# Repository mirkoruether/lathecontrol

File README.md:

# Pimp your lathe!
bla bla will be added later.

## Software Libraries
#### RotaryEncoder
https://github.com/mathertel/RotaryEncoder
http://www.mathertel.de/Arduino/RotaryEncoderLibrary.aspx

#### Display
http://www.lcdwiki.com/3.5inch_Arduino_Display-UNO#Program_Download
https://github.com/lcdwiki/LCDWIKI_gui
https://github.com/lcdwiki/LCDWIKI_kbv
https://github.com/adafruit/Adafruit_TouchScreen

## Hardware
#### Measuring Sticks (German):
https://www.wabeco-remscheid.de/catalog/category/view/s/anbaumessschieber/id/562/

#### Arduino Mega2560:
https://store.arduino.cc/arduino-mega-2560-rev3

#### Display
http://www.lcdwiki.com/3.5inch_Arduino_Display-UNO
https://www.amazon.de/gp/product/B07K2YCSJD/

## Other Links
http://www.mtahlers.de/index.php/diverses/messschieberanzeige

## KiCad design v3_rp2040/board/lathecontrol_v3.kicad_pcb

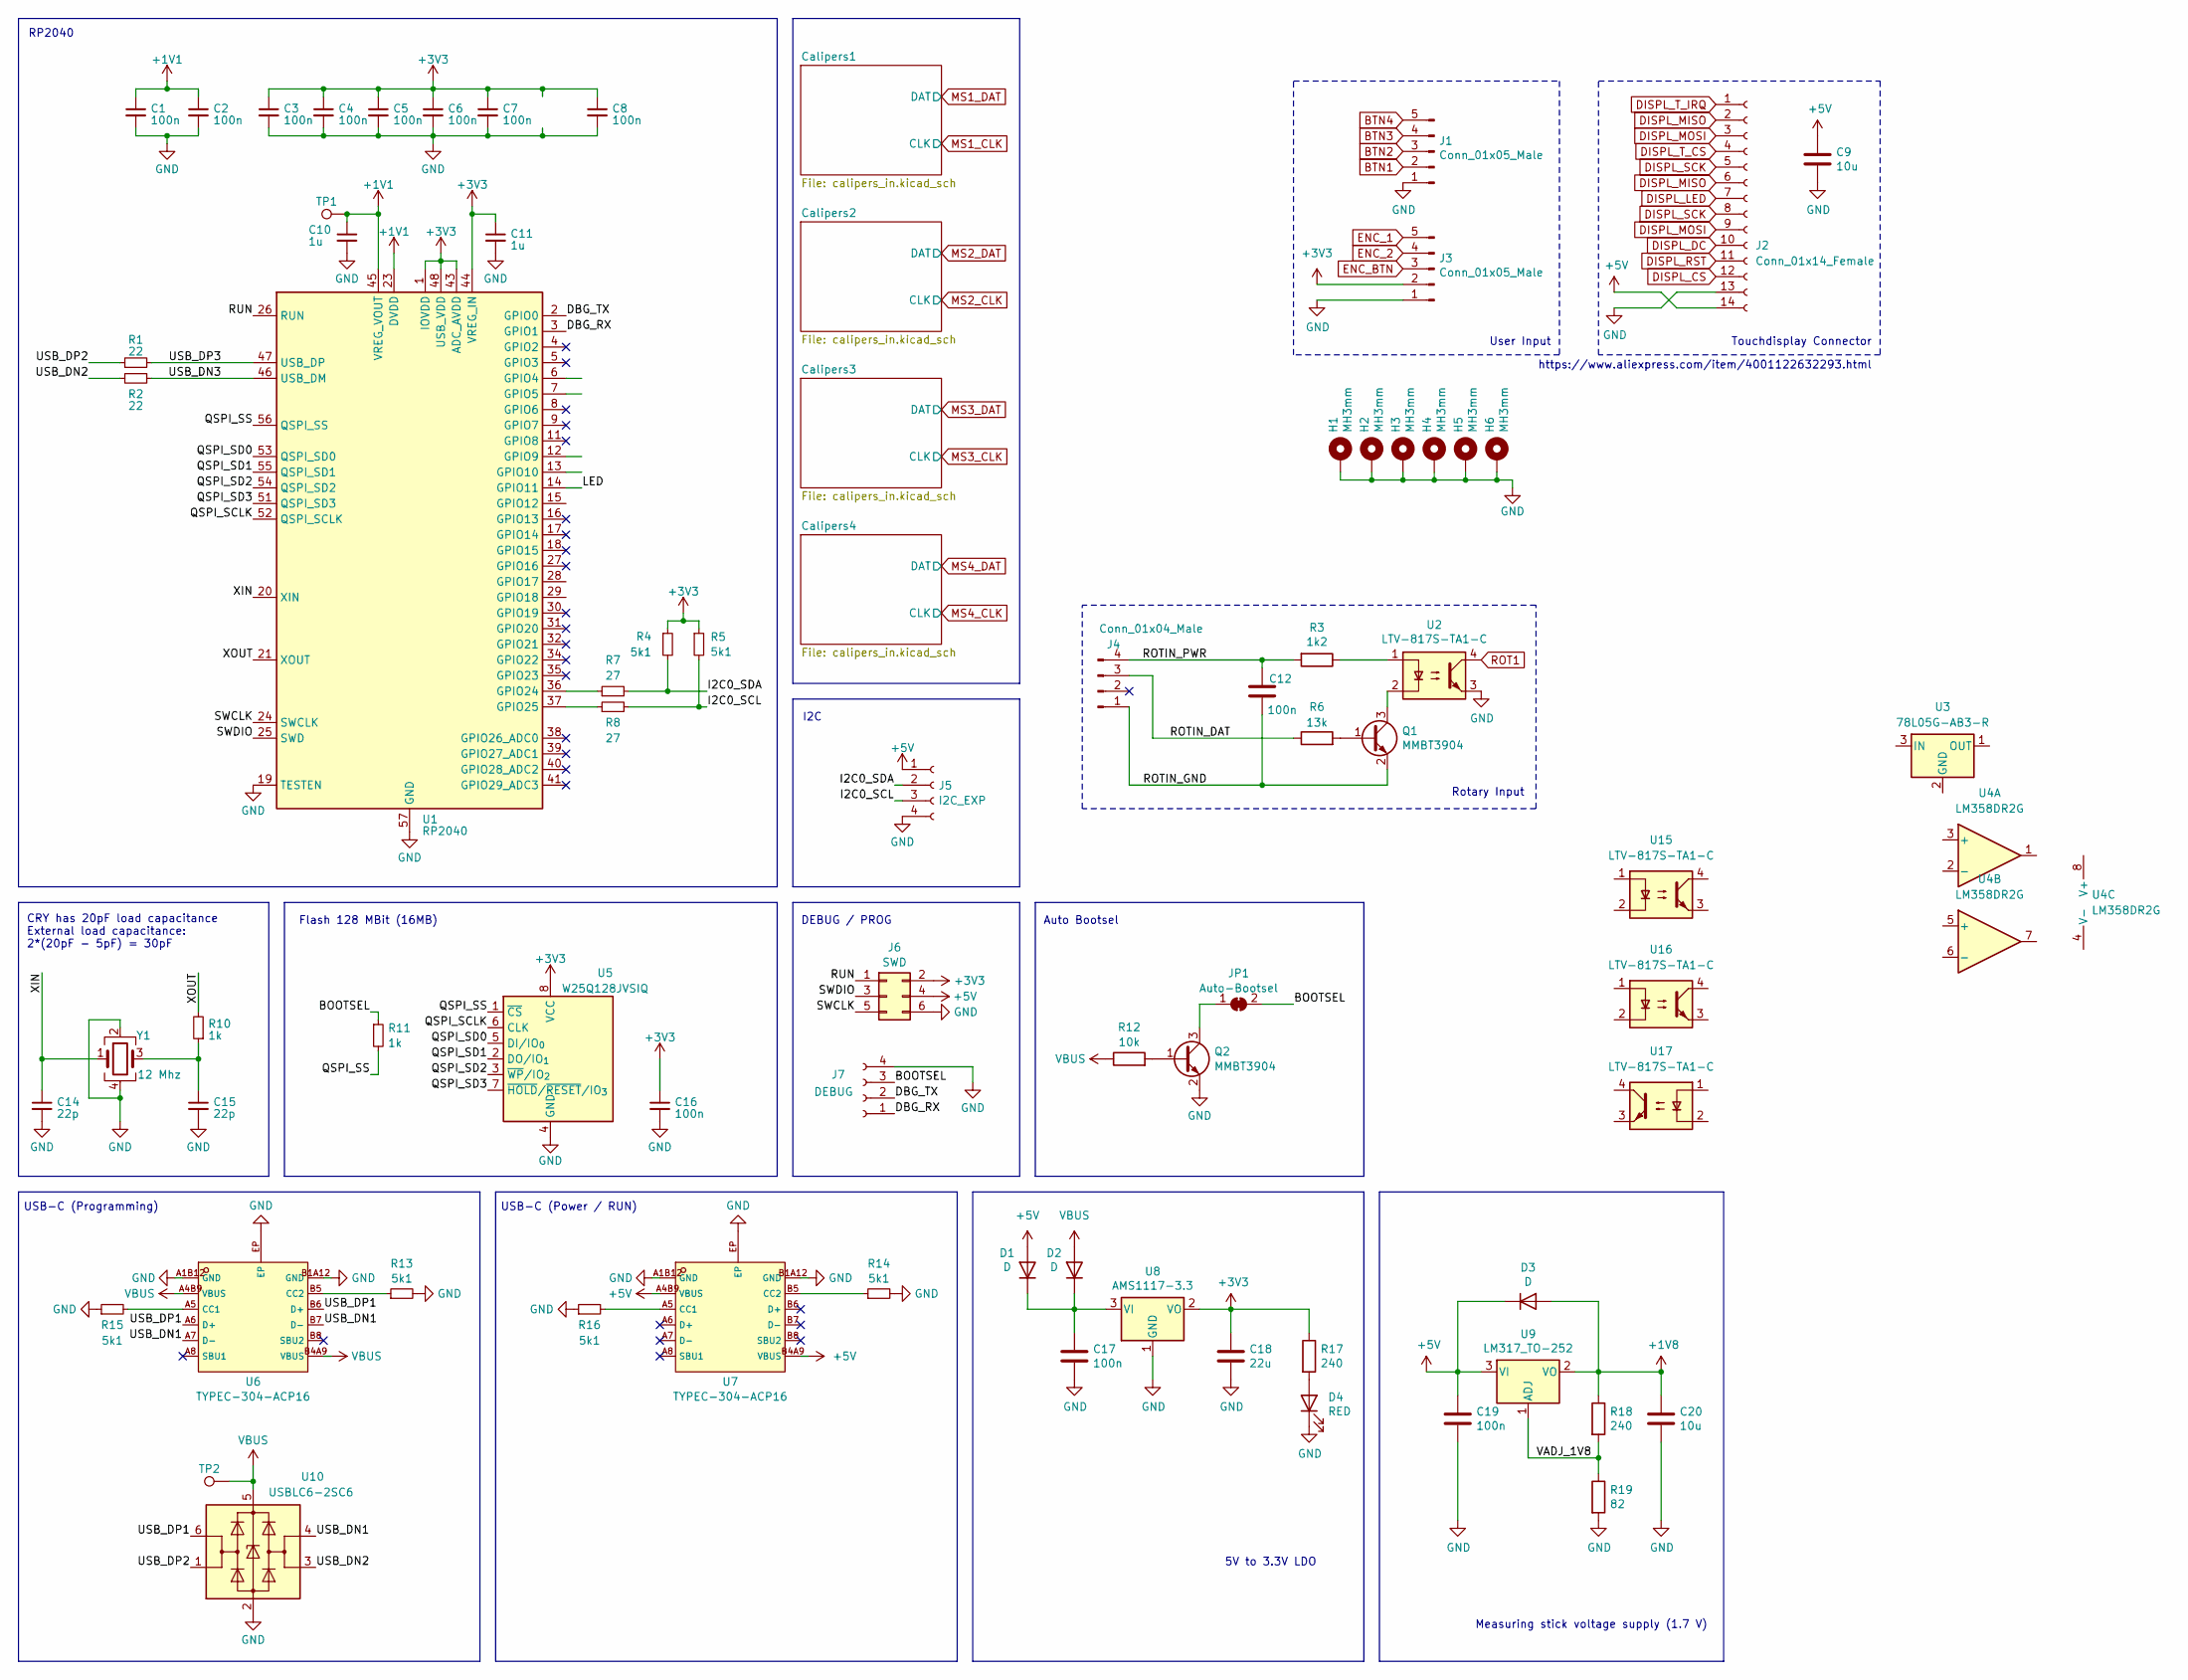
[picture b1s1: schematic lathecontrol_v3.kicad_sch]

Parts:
C1, C2, C3, C4, C5, C6, C7, C8, C16: 100n; C_0402_1005Metric; LCSC C1525
C9, C20: 10u; C_0805_2012Metric; LCSC C13585
C10, C11: 1u; C_0402_1005Metric; LCSC C52923
C12, C17, C19: 100n; C_0603_1608Metric; LCSC C14663
C14, C15: 22p; C_0402_1005Metric; LCSC C1555
C18: 22u; C_0805_2012Metric; LCSC C45783
D1, D2, D3: D; D_SOD-123F; LCSC C64898
D4: RED; LED_0603_1608Metric; LCSC C2286
H1, H2, H3, H4, H5, H6: MH3mm; MountingHole_3mm_Pad
J1: Conn_01x05_Male; PinHeader_1x06_P2.54mm_Horizontal
J2: Conn_01x14_Female; PinSocket_1x14_P2.54mm_Vertical
J3: Conn_01x05_Male; PinHeader_1x05_P2.54mm_Horizontal
J4: Conn_01x04_Male; PinHeader_1x04_P2.54mm_Horizontal
J5: I2C_EXP; PinHeader_1x04_P2.54mm_Vertical; LCSC C2691448
J6: SWD; PinHeader_2x03_P2.54mm_Vertical; LCSC C65114
J7: DEBUG; PinHeader_1x04_P2.54mm_Vertical; LCSC C2691448
JP1: Auto-Bootsel; R_0603_1608Metric; LCSC C21189
Q1: MMBT3904; SOT-23
Q2: MMBT3904; SOT-23; LCSC C20526
R1, R2: 22; R_0402_1005Metric; LCSC C25092
R3: 1k2; R_0805_2012Metric; LCSC C17379
R4, R5, R13, R14, R15, R16: 5k1; R_0603_1608Metric; LCSC C23186
R6: 13k; R_0603_1608Metric; LCSC C22797
R7, R8: 27; R_0603_1608Metric; LCSC C25190
R10, R11: 1k; R_0402_1005Metric; LCSC C11702
R12: 10k; R_0402_1005Metric; LCSC C25744
R17, R18: 240; R_0603_1608Metric; LCSC C23350
R19: 82; R_0603_1608Metric; LCSC C23255
TP1, TP2: TestPoint; TestPoint_Pad_D1.5mm
U1: RP2040; RP2040-QFN-56; LCSC C2040
U2, U15, U16, U17: LTV-817S-TA1-C; SMDIP-4_W9.53mm; LCSC C109227
U3: 78L05G-AB3-R; SOT-89-3; LCSC C71136
U4: LM358DR2G; SOIC-8_3.9x4.9mm_P1.27mm; LCSC C7950
U5: W25Q128JVSIQ; SOIC-8_5.3x5.3mm_P1.27mm; LCSC C97521
U6, U7: TYPEC-304-ACP16; USB-C-SMD_TYPE-C-16P-1; LCSC C2982555
U8: AMS1117-3.3; SOT-223-3_TabPin2; LCSC C6186
U9: LM317_TO-252; TO-252-2; LCSC C75510
U10: USBLC6-2SC6; SOT-23-6; LCSC C2827654
Y1: 12 Mhz; OSC-SMD_4P-L3.2-W2.5-BL; LCSC C9002

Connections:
+1V1: C1.1, C2.1, C10.1, TP1.1 (1_1), U1.23 (DVDD), U1.45 (VREG_VOUT), U1.50 (DVDD)
+1V8: C20.1, D3.2 (A), R18.1, U9.2 (VO); also elsewhere on the board
+3V3: C3.1, C4.1, C5.1, C6.1, C7.1, C8.1, C11.1, C16.1, C18.1, J3.2, J6.2, R4.1, R5.1, R17.1, U1.1 (IOVDD), U1.10 (IOVDD), U1.22 (IOVDD), U1.33 (IOVDD), U1.42 (IOVDD), U1.43 (ADC_AVDD), U1.44 (VREG_IN), U1.48 (USB_VDD), U1.49 (IOVDD), U5.8 (VCC), U8.2 (VO); also elsewhere on the board
+5V: C9.1, C19.1, D1.2 (A), D3.1 (K), J2.14, J5.1, J6.4, U7.A4B9 (VBUS), U7.B4A9 (VBUS), U9.3 (VI)
/BOOTSEL: J7.3, JP1.2 (B), R11.1
/DBG_RX: J7.1, U1.3 (GPIO1)
/DBG_TX: J7.2, U1.2 (GPIO0)
/I2C0_SCL: J5.3, R5.2, R8.2
/I2C0_SDA: J5.2, R4.2, R7.2
/LED: U1.14 (GPIO11)
/QSPI_SCLK: U1.52 (QSPI_SCLK), U5.6 (CLK)
/QSPI_SD0: U1.53 (QSPI_SD0), U5.5 (DI/IO_{0})
/QSPI_SD1: U1.55 (QSPI_SD1), U5.2 (DO/IO_{1})
/QSPI_SD2: U1.54 (QSPI_SD2), U5.3 (~WP/IO_{2})
/QSPI_SD3: U1.51 (QSPI_SD3), U5.7 (~HOLD/~RESET/IO_{3})
/QSPI_SS: R11.2, U1.56 (QSPI_SS), U5.1 (~CS)
/ROTIN_DAT: J4.3, R6.1
/ROTIN_GND: C12.2, J4.1, Q1.2 (E)
/ROTIN_PWR: C12.1, J4.4, R3.2
/RUN: J6.1, U1.26 (RUN)
/SWCLK: J6.5, U1.24 (SWCLK)
/SWDIO: J6.3, U1.25 (SWD)
/USB_DN1: U6.A7 (D-), U6.B7 (D-), U10.4 (I/O2)
/USB_DN2: R2.2, U10.3 (I/O2)
/USB_DN3: R2.1, U1.46 (USB_DM)
/USB_DP1: U6.A6 (D+), U6.B6 (D+), U10.6 (I/O1)
/USB_DP2: R1.1, U10.1 (I/O1)
/USB_DP3: R1.2, U1.47 (USB_DP)
/VADJ_1V8: R18.2, R19.1, U9.1 (ADJ)
/XIN: C14.1, U1.20 (XIN), Y1.1
/XOUT: R10.2, U1.21 (XOUT)
BTN1: J1.2
BTN2: J1.3
BTN3: J1.4
BTN4: J1.5
DISPL_CS: J2.12
DISPL_DC: J2.10
DISPL_LED: J2.7
DISPL_MISO: J2.2, J2.6
DISPL_MOSI: J2.3, J2.9
DISPL_RST: J2.11
DISPL_SCK: J2.5, J2.8
DISPL_T_CS: J2.4
DISPL_T_IRQ: J2.1
ENC_1: J3.5
ENC_2: J3.4
ENC_BTN: J3.3
GND: C1.2, C2.2, C3.2, C4.2, C5.2, C6.2, C7.2, C8.2, C9.2, C10.2, C11.2, C14.2, C15.2, C16.2, C17.2, C18.2, C19.2, C20.2, D4.1 (K), H1.1 (1_1), H2.1 (1_1), H3.1 (1_1), H4.1 (1_1), H5.1 (1_1), H6.1 (1_1), J1.1, J2.13, J3.1, J5.4, J6.6, J7.4, Q2.2 (E), R13.2, R14.2, R15.1, R16.1, R19.2, U1.19 (TESTEN), U1.57 (GND), U2.3, U5.4 (GND), U6.A1B12 (GND), U6.B1A12 (GND), U6.EP, U7.A1B12 (GND), U7.B1A12 (GND), U7.EP, U8.1 (GND), U10.2 (GND), Y1.2, Y1.4; also elsewhere on the board
unnamed: C15.1, R10.1, Y1.3
unnamed: C17.1, D1.1 (K), D2.1 (K), U8.3 (VI)
unnamed: D4.2 (A), R17.2
unnamed: JP1.1 (A), Q2.3 (C)
unnamed: Q1.1 (B), R6.2
unnamed: Q1.3 (C), U2.2
unnamed: Q2.1 (B), R12.2
unnamed: R3.1, U2.1
unnamed: R7.1, U1.36 (GPIO24)
unnamed: R8.1, U1.37 (GPIO25)
unnamed: R15.2, U6.A5 (CC1)
unnamed: R13.1, U6.B5 (CC2)
unnamed: R16.2, U7.A5 (CC1)
unnamed: R14.1, U7.B5 (CC2)
ROT1: U2.4
VBUS: D2.2 (A), R12.1, TP2.1 (1_1), U6.A4B9 (VBUS), U6.B4A9 (VBUS), U10.5 (VBUS)

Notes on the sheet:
5V to 3.3V LDO
RP2040
Rotary Input
Flash 128 MBit (16MB)
https://www.aliexpress.com/item/4001122632293.html
USB-C (Programming)
Touchdisplay Connector
I2C
CRY has 20pF load capacitance External load capacitance: 2*(20pF - 5pF) = 30pF
Measuring stick voltage supply (1.7 V)
Auto Bootsel
USB-C (Power / RUN)
User Input
DEBUG / PROG

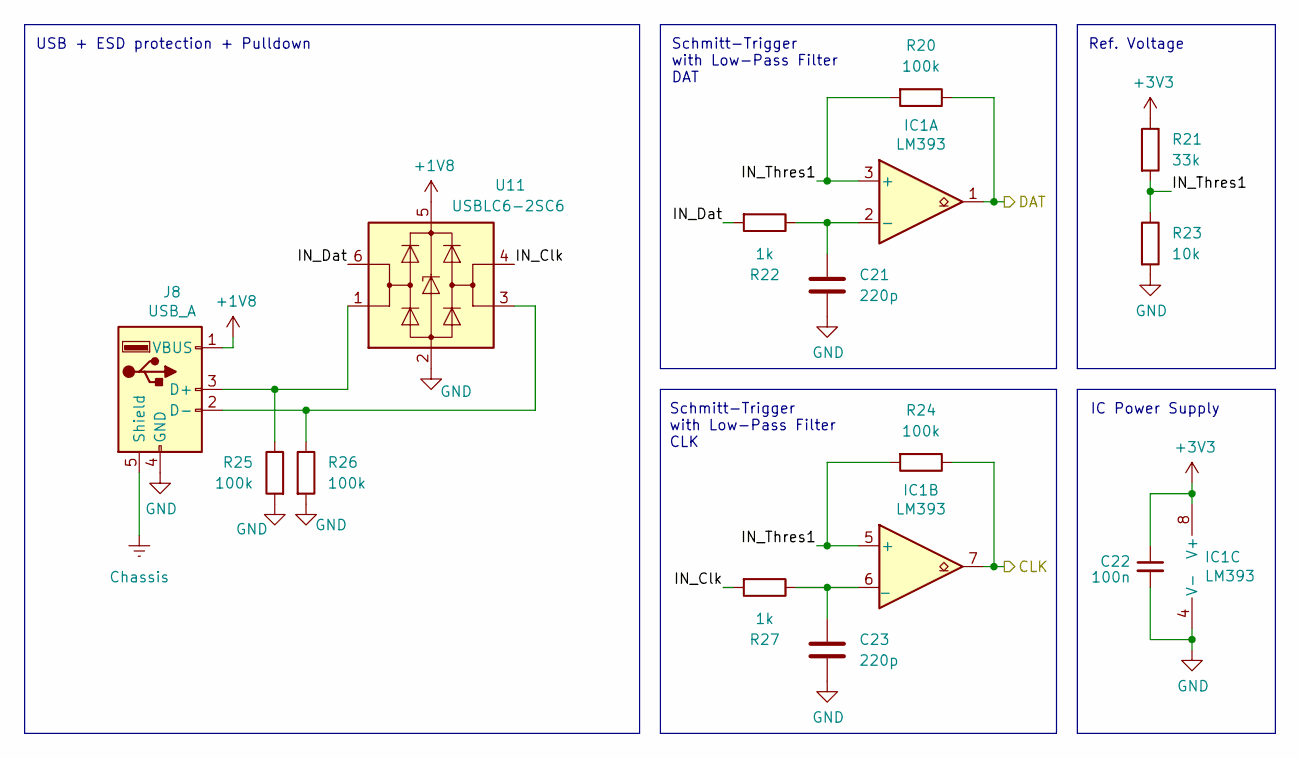
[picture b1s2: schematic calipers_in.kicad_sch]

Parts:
C21, C23: 220p; C_0402_1005Metric; LCSC C1530
C22: 100n; C_0402_1005Metric; LCSC C1525
IC1: LM393; SOIC-8_3.9x4.9mm_P1.27mm
J8: USB_A; USB_A_Upright_C26235; LCSC C26235
R20, R24, R25, R26: 100k; R_0402_1005Metric; LCSC C25741
R21: 33k; R_0402_1005Metric; LCSC C25779
R22, R27: 1k; R_0402_1005Metric; LCSC C11702
R23: 10k; R_0402_1005Metric; LCSC C25744
U11: USBLC6-2SC6; SOT-23-6; LCSC C2827654

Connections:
+1V8: J8.1 (VBUS), U11.5 (VBUS); also elsewhere on the board
+3V3: C22.1, IC1.8 (V+), R21.1; also elsewhere on the board
/Calipers1/IN_Clk: R27.2, U11.4 (I/O2)
/Calipers1/IN_Dat: R22.2, U11.6 (I/O1)
/Calipers1/IN_Thres1: IC1.3 (+), IC1.5 (+), R20.2, R21.2, R23.1, R24.2
Chassis: J8.5 (Shield); also elsewhere on the board
GND: C21.2, C22.2, C23.2, IC1.4 (V-), J8.4 (GND), R23.2, R25.2, R26.2, U11.2 (GND); also elsewhere on the board
MS1_CLK: IC1.7, R24.1
MS1_DAT: IC1.1, R20.1
unnamed: C21.1, IC1.2 (-), R22.1
unnamed: C23.1, IC1.6 (_), R27.1
unnamed: J8.3 (D+), R25.1, U11.1 (I/O1)
unnamed: J8.2 (D-), R26.1, U11.3 (I/O2)

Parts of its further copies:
C24, C26, C27, C29, C30, C32: 220p; C_0402_1005Metric; LCSC C1530
C25, C28, C31: 100n; C_0402_1005Metric; LCSC C1525
IC2, IC3, IC4: LM393; SOIC-8_3.9x4.9mm_P1.27mm
J9, J10, J11: USB_A; USB_A_Upright_C26235; LCSC C26235
R28, R32, R33, R34, R36, R40, R41, R42, R44, R48, R49, R50: 100k; R_0402_1005Metric; LCSC C25741
R29, R37, R45: 33k; R_0402_1005Metric; LCSC C25779
R30, R35, R38, R43, R46, R51: 1k; R_0402_1005Metric; LCSC C11702
R31, R39, R47: 10k; R_0402_1005Metric; LCSC C25744
U12, U13, U14: USBLC6-2SC6; SOT-23-6; LCSC C2827654

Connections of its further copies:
+1V8: J9.1 (VBUS), J10.1 (VBUS), J11.1 (VBUS), U12.5 (VBUS), U13.5 (VBUS), U14.5 (VBUS); also elsewhere on the board
+3V3: C25.1, C28.1, C31.1, IC2.8 (V+), IC3.8 (V+), IC4.8 (V+), R29.1, R37.1, R45.1; also elsewhere on the board
/Calipers2/IN_Clk: R35.2, U12.4 (I/O2)
/Calipers2/IN_Dat: R30.2, U12.6 (I/O1)
/Calipers2/IN_Thres1: IC2.3 (+), IC2.5 (+), R28.2, R29.2, R31.1, R32.2
/Calipers3/IN_Clk: R43.2, U13.4 (I/O2)
/Calipers3/IN_Dat: R38.2, U13.6 (I/O1)
/Calipers3/IN_Thres1: IC3.3 (+), IC3.5 (+), R36.2, R37.2, R39.1, R40.2
/Calipers4/IN_Clk: R51.2, U14.4 (I/O2)
/Calipers4/IN_Dat: R46.2, U14.6 (I/O1)
/Calipers4/IN_Thres1: IC4.3 (+), IC4.5 (+), R44.2, R45.2, R47.1, R48.2
Chassis: J9.5 (Shield), J10.5 (Shield), J11.5 (Shield); also elsewhere on the board
GND: C24.2, C25.2, C26.2, C27.2, C28.2, C29.2, C30.2, C31.2, C32.2, IC2.4 (V-), IC3.4 (V-), IC4.4 (V-), J9.4 (GND), J10.4 (GND), J11.4 (GND), R31.2, R33.2, R34.2, R39.2, R41.2, R42.2, R47.2, R49.2, R50.2, U12.2 (GND), U13.2 (GND), U14.2 (GND); also elsewhere on the board
MS2_CLK: IC2.7, R32.1
MS2_DAT: IC2.1, R28.1
MS3_CLK: IC3.7, R40.1
MS3_DAT: IC3.1, R36.1
MS4_CLK: IC4.7, R48.1
MS4_DAT: IC4.1, R44.1
unnamed: C24.1, IC2.2 (-), R30.1
unnamed: C26.1, IC2.6 (_), R35.1
unnamed: C27.1, IC3.2 (-), R38.1
unnamed: C29.1, IC3.6 (_), R43.1
unnamed: C30.1, IC4.2 (-), R46.1
unnamed: C32.1, IC4.6 (_), R51.1
unnamed: J9.3 (D+), R33.1, U12.1 (I/O1)
unnamed: J9.2 (D-), R34.1, U12.3 (I/O2)
unnamed: J10.3 (D+), R41.1, U13.1 (I/O1)
unnamed: J10.2 (D-), R42.1, U13.3 (I/O2)
unnamed: J11.3 (D+), R49.1, U14.1 (I/O1)
unnamed: J11.2 (D-), R50.1, U14.3 (I/O2)

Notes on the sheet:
IC Power Supply
Schmitt-Trigger with Low-Pass Filter DAT
USB + ESD protection + Pulldown
Schmitt-Trigger with Low-Pass Filter CLK
Ref. Voltage

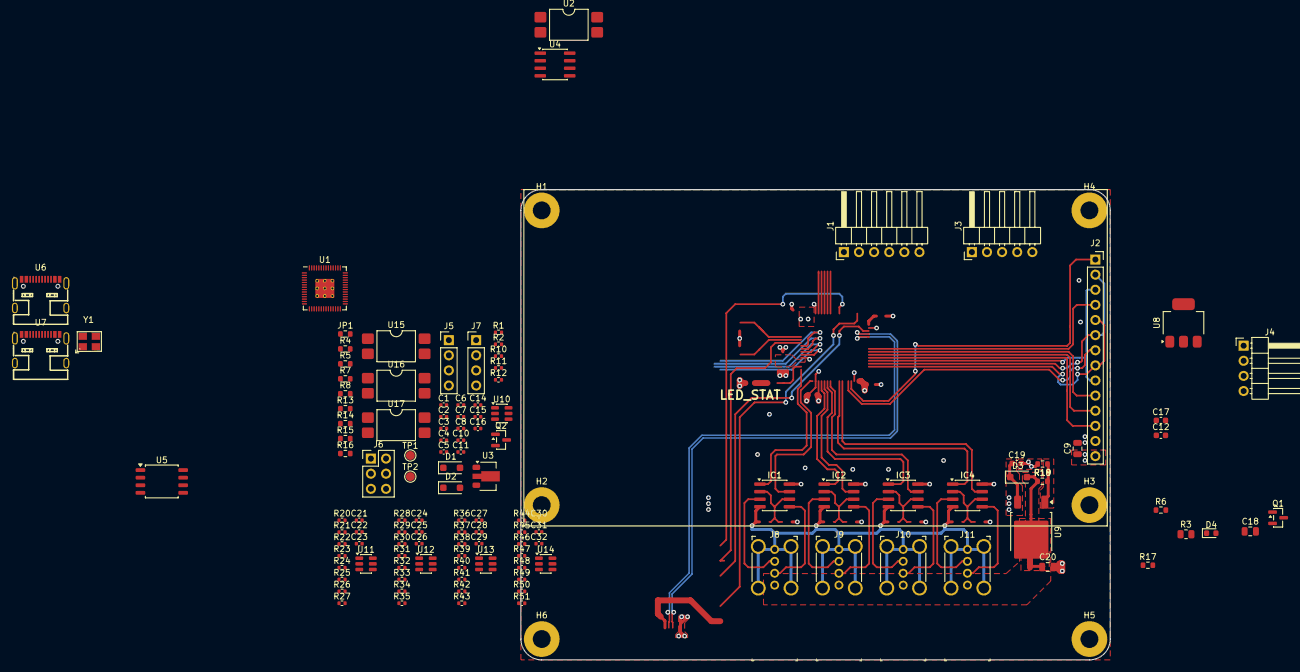
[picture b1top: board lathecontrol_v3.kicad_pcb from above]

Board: 4 copper layers, 99.0 x 79.0 mm, 129 parts (0 on the bottom side), 86 nets.

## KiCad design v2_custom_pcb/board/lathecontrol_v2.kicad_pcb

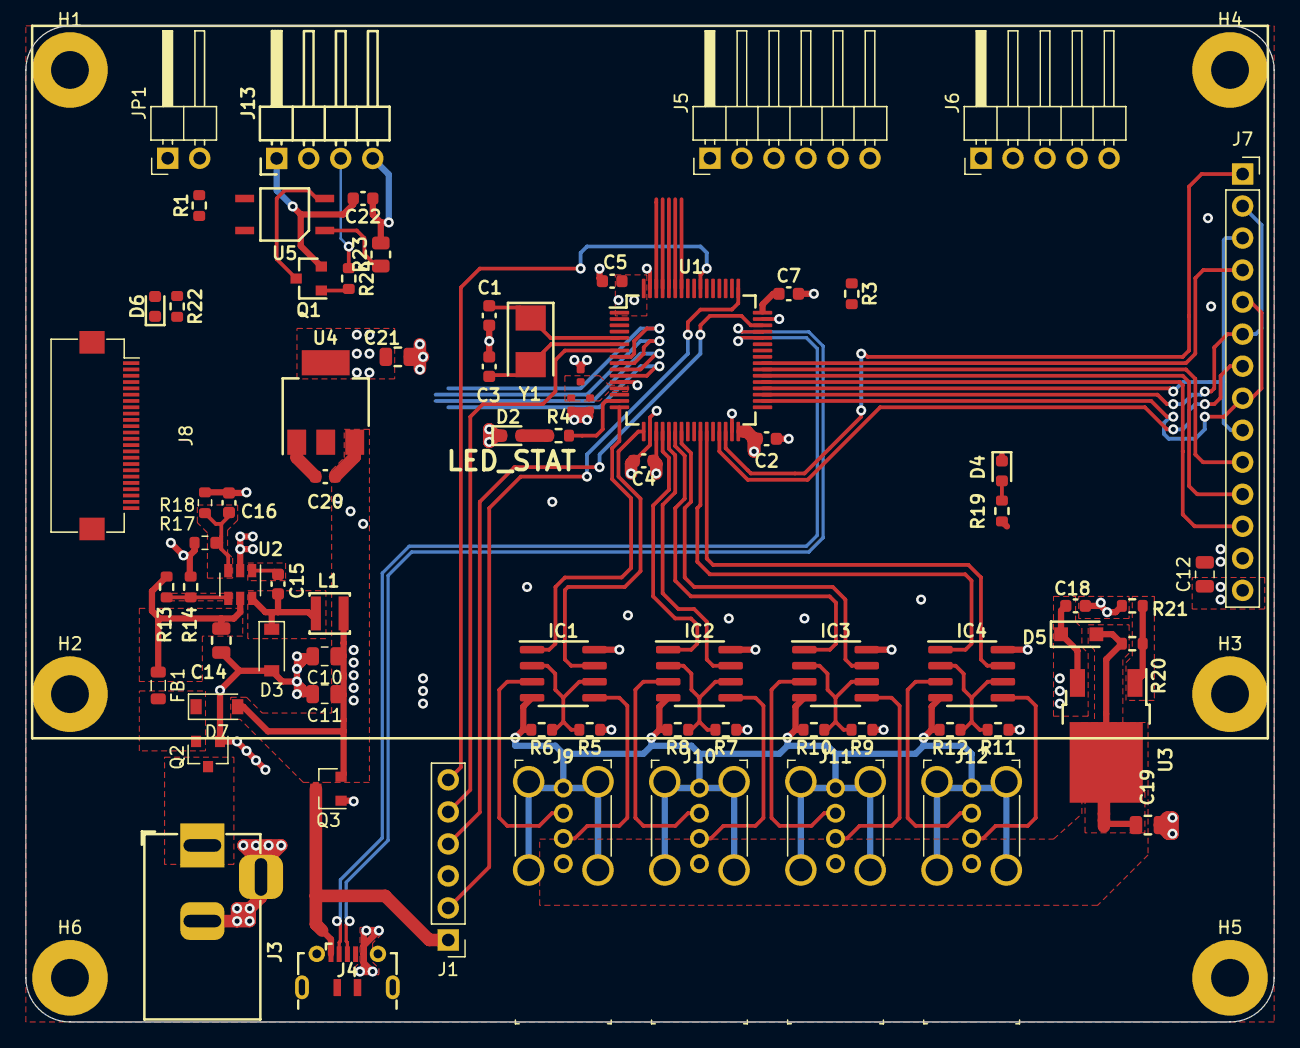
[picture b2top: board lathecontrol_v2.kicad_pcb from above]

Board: 4 copper layers, 99.0 x 79.0 mm, 81 parts (0 on the bottom side), 78 nets.

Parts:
C1, C3, C16: 30p; C_0603_1608Metric
C2, C4, C5, C7, C15, C18, C20, C22: 100n; C_0603_1608Metric
C8: 1u; L_0402_1005Metric
C9: 10n; L_0402_1005Metric
C10, C11, C12, C14, C19: 10u; C_0805_2012Metric
C21: 22u; C_0805_2012Metric
D2, D4, D6: RED; LED_0603_1608Metric
D3, D7: D_Schottky; D_SOD-123
D5: D; D_SOD-123F
FB1: 600 @ 600MHz; L_0805_2012Metric
H1, H2, H3, H4, H5, H6: MH3mm; MountingHole_3mm_Pad
IC1, IC2, IC3, IC4: LM393; SOIC-8_3.9x4.9mm_P1.27mm
J1: Conn_01x06_Male; PinHeader_1x06_P2.54mm_Vertical
J3: Barrel_Jack_Switch; BarrelJack_Horizontal_DC-005-20A
J4: USB_B_Micro; USB_Micro-B_SHOU_HAN_MicroXNJ
J5: Conn_01x05_Male; PinHeader_1x06_P2.54mm_Horizontal
J6: Conn_01x05_Male; PinHeader_1x05_P2.54mm_Horizontal
J7: Conn_01x14_Female; PinSocket_1x14_P2.54mm_Vertical
J8: Conn_01x24; FFC_FPC_1x24_DualSide_JUSHUO_AFC24-S24FIC-00
J9, J10, J11, J12: USB_A; USB_A_Upright_C26235
J13: Conn_01x04_Male; PinHeader_1x04_P2.54mm_Horizontal
JP1: BOOTSEL; PinHeader_1x02_P2.54mm_Horizontal
L1: 4U7; L_3012_SMD3.0x3.0x1.2mm
L2: 39n; L_0402_1005Metric
Q1: MMBT3904; SOT-23
Q2, Q3: AO3401A; SOT-23
R1, R14: 10k; R_0603_1608Metric
R3: 1k5; R_0603_1608Metric
R4, R20, R22: 240; R_0603_1608Metric
R5, R7, R9, R11, R24: 13k; R_0603_1608Metric
R6, R8, R10, R12: 3k3; R_0603_1608Metric
R13, R17: 24k; R_0603_1608Metric
R18: 120k; R_0603_1608Metric
R19: 620; R_0603_1608Metric
R21: 82; R_0603_1608Metric
R23: 1k2; R_0805_2012Metric
U1: STM32F103RBTx; LQFP-64_10x10mm_P0.5mm
U2: MP2451DT-LF-Z; SOT-23-6
U3: LM317_TO-252; TO-252-2
U4: AMS1117-3.3; SOT-223-3_TabPin2
U5: Everlight_Elec_EL357N; SOP-4_4.1x4.4x2.54P
Y1: 8MHz; Crystal_SMD_5032-2Pin_5.0x3.2mm

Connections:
+1V8: C19.1, D5.2, J9.1, J10.1, J11.1, J12.1, R20.1, U3.2
+3.3VA: C8.1, C9.1, L2.2, U1.13
+3V3: C2.1, C4.1, C5.1, C7.1, C21.1, IC1.8, IC2.8, IC3.8, IC4.8, J6.2, J8.1, J8.12, JP1.1, L2.1, R3.1, R5.1, R7.1, R9.1, R11.1, R22.1, U1.1, U1.19, U1.32, U1.48, U1.64, U4.2
+5V: C10.1, C11.1, C12.1, C16.2, C18.1, C20.1, D5.1, D7.2, J7.14, J8.8, J8.21, L1.2, Q3.2, R18.2, R19.1, U3.3, U4.3
/BOOT0: JP1.2, R1.2, U1.60
/LED_STAT1: R4.1, U1.15
/Measurestick Input 1/IN_Clk: IC1.5, J9.2
/Measurestick Input 1/IN_Dat: IC1.3, J9.3
/Measurestick Input 1/IN_Thres1: IC1.2, IC1.6, R5.2, R6.1
/Measurestick Input 2/IN_Clk: IC2.5, J10.2
/Measurestick Input 2/IN_Dat: IC2.3, J10.3
/Measurestick Input 2/IN_Thres1: IC2.2, IC2.6, R7.2, R8.1
/Measurestick Input 3/IN_Clk: IC3.5, J11.2
/Measurestick Input 3/IN_Dat: IC3.3, J11.3
/Measurestick Input 3/IN_Thres1: IC3.2, IC3.6, R9.2, R10.1
/Measurestick Input 4/IN_Clk: IC4.5, J12.2
/Measurestick Input 4/IN_Dat: IC4.3, J12.3
/Measurestick Input 4/IN_Thres1: IC4.2, IC4.6, R11.2, R12.1
/OSC_IN: C1.1, U1.5, Y1.1
/OSC_OUT: C3.1, U1.6, Y1.2
/Power/5VBST: C15.1, U2.1
/Power/5VEN: R13.2, R14.2, U2.4
/Power/5VFB: C16.1, R17.2, R18.1, U2.3
/Power/5VSW: C15.2, D3.1, L1.1, U2.6
/Power/VADJ_1V8: R20.2, R21.1, U3.1
/Power/VCC_MID: D7.1, FB1.2, Q2.2
/Rotation Input/ROTIN_DAT: J13.3, R24.1
/Rotation Input/ROTIN_GND: C22.2, J13.1, Q1.2
/Rotation Input/ROTIN_PWR: C22.1, J13.4, R23.2
ADC1: J8.16, U1.8
ADC2: J8.17, U1.9
ADC3: J8.18, U1.10
ADC4: J8.19, U1.11
BTN1: J5.2, U1.57
BTN2: J5.3, U1.56
BTN3: J5.4, U1.52
BTN4: J5.5, U1.51
DISPL_CS: J7.12, U1.37
DISPL_DC: J7.10, U1.39
DISPL_LED: J7.7, U1.29
DISPL_MISO: J7.2, J7.6, U1.35
DISPL_MOSI: J7.3, J7.9, U1.36
DISPL_RST: J7.11, U1.38
DISPL_SCK: J7.5, J7.8, U1.34
DISPL_T_CS: J7.4, U1.40
DISPL_T_IRQ: J7.1, U1.30
ENC_1: J6.5, U1.42
ENC_2: J6.4, U1.43
ENC_BTN: J6.3, U1.41
GND: C1.2, C2.2, C3.2, C4.2, C5.2, C7.2, C8.2, C9.2, C10.2, C11.2, C12.2, C14.2, C18.2, C19.2, C20.2, C21.2, D2.1, D3.2, D4.1, D6.1, H1.1, H2.1, H3.1, H4.1, H5.1, H6.1, IC1.4, IC2.4, IC3.4, IC4.4, J1.3, J3.2, J3.3, J4.5, J5.1, J6.1, J7.13, J8.7, J8.11, J8.15, J8.20, J8.24, J9.4, J9.5, J10.4, J10.5, J11.4, J11.5, J12.4, J12.5, Q2.1, Q3.1, R1.1, R6.2, R8.2, R10.2, R12.2, R14.1, R17.1, R21.2, U1.12, U1.18, U1.31, U1.47, U1.63, U2.2, U4.1, U5.3
I2C_SCL: J8.9, U1.61
I2C_SDA: J8.10, U1.62
IN_+5V: J1.1, J4.1, Q3.3
IN_VCC: J3.1, Q2.3
MS1_CLK: IC1.7, U1.17
MS1_DAT: IC1.1, U1.16
MS2_CLK: IC2.7, U1.21
MS2_DAT: IC2.1, U1.20
MS3_CLK: IC3.7, U1.23
MS3_DAT: IC3.1, U1.22
MS4_CLK: IC4.7, U1.27
MS4_DAT: IC4.1, U1.26
NRST: J1.5, U1.7
unnamed: D2.2, R4.2
unnamed: D4.2, R19.2
unnamed: D6.2, R22.2
unnamed: Q1.1, R24.2
unnamed: Q1.3, U5.2
unnamed: R23.1, U5.1
ROT1: U1.2, U5.4
SWCLK: J1.2, U1.49
SWDIO: J1.4, U1.46
SWD_SWO: J1.6, U1.55
UART_RX: J8.23, U1.59
UART_TX: J8.22, U1.58
USB_D+: J4.3, R3.2, U1.45
USB_D-: J4.2, U1.44
VCC: C14.1, FB1.1, R13.1, U2.5

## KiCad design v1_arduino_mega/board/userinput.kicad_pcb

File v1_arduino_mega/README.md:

# Pimp your lathe!
bla bla will be added later.

## Software Libraries
#### RotaryEncoder
https://github.com/mathertel/RotaryEncoder \
http://www.mathertel.de/Arduino/RotaryEncoderLibrary.aspx 

#### Display
http://www.lcdwiki.com/3.5inch_Arduino_Display-UNO#Program_Download \
https://github.com/lcdwiki/LCDWIKI_gui \
https://github.com/lcdwiki/LCDWIKI_kbv \
https://github.com/adafruit/Adafruit_TouchScreen 

## Hardware
#### Measuring Sticks (German):
https://www.wabeco-remscheid.de/catalog/category/view/s/anbaumessschieber/id/562/

#### Arduino Mega2560:
https://store.arduino.cc/arduino-mega-2560-rev3

#### Display
http://www.lcdwiki.com/3.5inch_Arduino_Display-UNO \
https://www.amazon.de/gp/product/B07K2YCSJD/ 

## Other Links
#### Very helpful project
http://www.mtahlers.de/index.php/diverses/messschieberanzeige

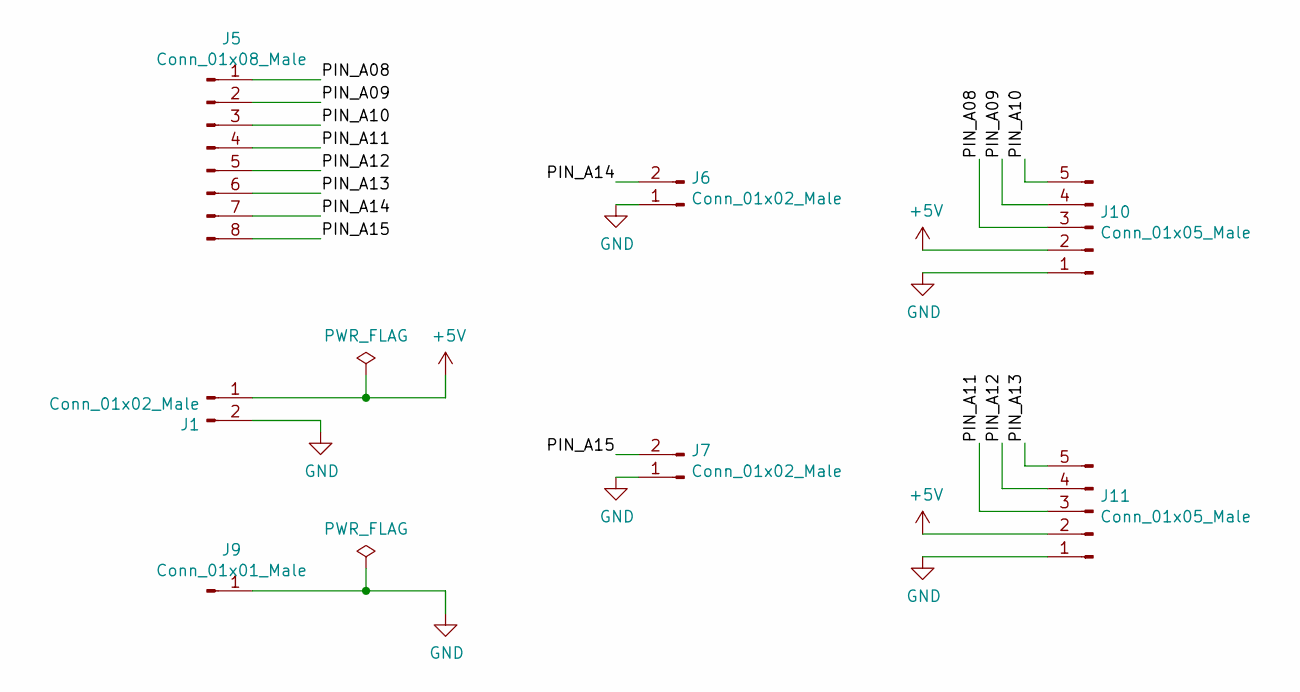
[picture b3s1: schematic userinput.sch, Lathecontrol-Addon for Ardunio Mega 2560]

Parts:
J1, J6, J7: Conn_01x02_Male; PinHeader_1x02_P2.54mm_Horizontal
J5: Conn_01x08_Male; PinHeader_1x08_P2.54mm_Vertical
J9: Conn_01x01_Male; PinHeader_1x01_P2.54mm_Vertical
J10, J11: Conn_01x05_Male; PinHeader_1x05_P2.54mm_Horizontal

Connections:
+5V: J1.1, J10.2, J11.2
/PIN_A08: J5.1, J10.3
/PIN_A09: J5.2, J10.4
/PIN_A10: J5.3, J10.5
/PIN_A11: J5.4, J11.3
/PIN_A12: J5.5, J11.4
/PIN_A13: J5.6, J11.5
/PIN_A14: J5.7, J6.2
/PIN_A15: J5.8, J7.2
GND: J1.2, J6.1, J7.1, J9.1, J10.1, J11.1

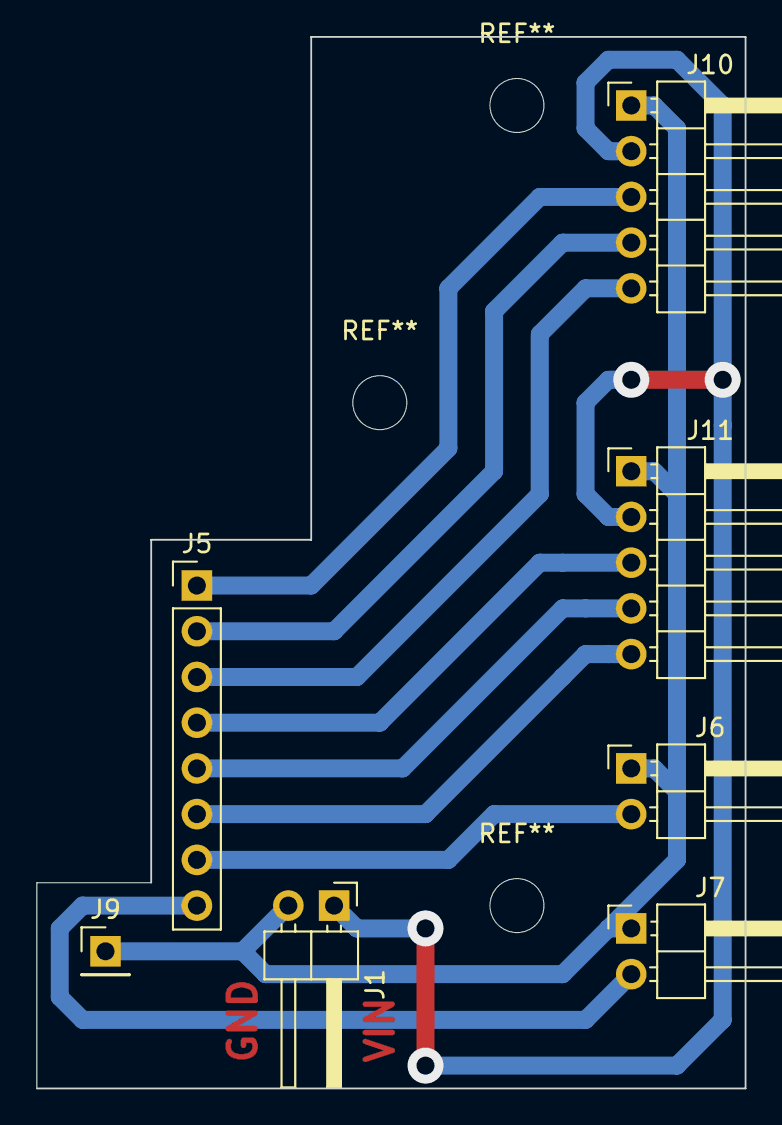
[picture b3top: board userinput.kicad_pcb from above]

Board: 2 copper layers, 39.4 x 58.4 mm, 7 parts (0 on the bottom side), 10 nets.

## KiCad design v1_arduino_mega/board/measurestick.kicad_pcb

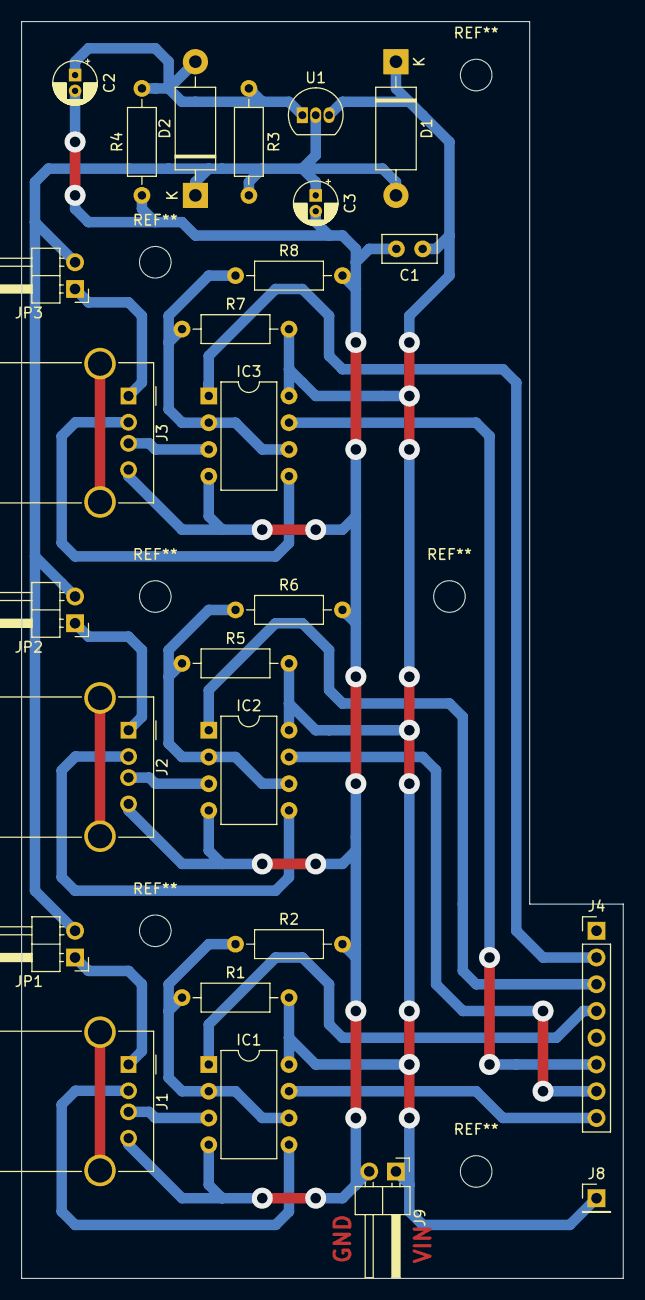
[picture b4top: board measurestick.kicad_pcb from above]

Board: 2 copper layers, 57.2 x 119.4 mm, 26 parts (0 on the bottom side), 22 nets.

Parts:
C1: 100n; C_Disc_D5.0mm_W2.5mm_P2.50mm
C2, C3: 2u2; CP_Radial_D4.0mm_P1.50mm
D1, D2: 1N5060; D_DO-15_P12.70mm_Horizontal
IC1, IC2, IC3: LM393; DIP-8_W7.62mm
J1, J2, J3: USB_A; USB_A_Molex_67643_Horizontal
J4: Conn_01x08_Male; PinHeader_1x08_P2.54mm_Vertical
J8: Conn_01x01_Male; PinHeader_1x01_P2.54mm_Vertical
J9: Conn_01x02_Male; PinHeader_1x02_P2.54mm_Horizontal
JP1, JP2, JP3: Jumper; PinHeader_1x02_P2.54mm_Horizontal
R1, R5, R7: 22k; R_Axial_DIN0207_L6.3mm_D2.5mm_P10.16mm_Horizontal
R2, R6, R8: 3k6; R_Axial_DIN0207_L6.3mm_D2.5mm_P10.16mm_Horizontal
R3: 1k; R_Axial_DIN0207_L6.3mm_D2.5mm_P10.16mm_Horizontal
R4: 360; R_Axial_DIN0207_L6.3mm_D2.5mm_P10.16mm_Horizontal
U1: LM317L_TO92; TO-92_Inline

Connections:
+5V: C1.1, D1.1, IC1.8, IC2.8, IC3.8, J8.1, J9.1, R1.2, R5.2, R7.2, U1.3
/1V7: C3.1, D1.2, D2.1, JP1.2, JP2.2, JP3.2, R3.2, U1.2
/IN_Clk1: IC1.5, J1.2
/IN_Clk2: IC2.5, J2.2
/IN_Clk3: IC3.5, J3.2
/IN_Dat1: IC1.3, J1.3
/IN_Dat2: IC2.3, J2.3
/IN_Dat3: IC3.3, J3.3
/IN_Thres1: IC1.2, IC1.6, R1.1, R2.1
/IN_Thres2: IC2.2, IC2.6, R5.1, R6.1
/IN_Thres3: IC3.2, IC3.6, R7.1, R8.1
/PIN_D15: IC3.1, J4.2
/PIN_D16: IC2.1, J4.3
/PIN_D17: IC1.1, J4.4
/PIN_D19: IC3.7, J4.6
/PIN_D20: IC2.7, J4.7
/PIN_D21: IC1.7, J4.8
/VADJ: C2.1, D2.2, R3.1, R4.2, U1.1
GND: C1.2, C2.2, C3.2, IC1.4, IC2.4, IC3.4, J1.4, J2.4, J3.4, J9.2, R2.2, R4.1, R6.2, R8.2
unnamed: J1.1, JP1.1
unnamed: J2.1, JP2.1
unnamed: J3.1, JP3.1

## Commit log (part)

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2020-05-26 Added simple rotary encoder test
2020-05-26 Removed check for USBCON
2020-06-16 Class for receiving data from measureing sticks
2020-12-27 Added KiCAD files
2020-12-27 Added KiCad lib files
2020-12-29 measuring stick readout
2020-12-29 Moved source code to sub folder "arduino"
2020-12-29 Revert "Create .gitmodules"
    This reverts commit e44962c60485e74c6a2ab994e036ca3884fc7c96.
2020-12-29 Added submodules (2nd try...)
2020-12-29 Reorganize project
2020-12-31 Added PinChangeInterrupt library
2020-12-31 Added timeout and non-floating-point getters to measuringstick
2020-12-31 Interrupt attachment with template programming
2021-01-02 Added GUI segment
2021-01-03 Moved GUI stuff to new class
2021-01-03 Added clk_rising_edge to MeasuringStick20Bit
2021-01-03 Gui "thread"safe and bool if new data avaiable after pushing bit to measuring stick
2021-01-03 Changed comma apperance
2021-01-03 Added OneButton lib
2021-01-04 First version / testing tomorrow :)
2021-01-04 Various fixes
2021-01-04 Renamed axis, show diameter
2021-01-04 Added suggested extensions
2021-02-10 Moved everything to v1 folder.
2021-02-10 Started schematic for STM32 version
2021-02-15 STM32 board: Power supply
2021-02-15 Switched to 64 pin STM32F103. Assigned pins
2021-02-15 Pins
2021-02-20 Added connectors
2021-02-20 Added LEDs
2021-02-21 Schematic finished (V0.1), Added footprints
2021-02-22 Changed MS DAT/CLK pins. Routed measuring stick input
2021-02-22 More routing
2021-02-23 MP2451 Routing according to datasheet
2021-02-23 Optimized measuring stick input
2021-02-28 Added stm32 pin config .ioc file
2021-03-09 Init PlatformIO project
2021-03-14 More PCB design
2021-03-14 Moved to 4 layer PCB. More routing
2021-03-29 Started current loop output for frequency converter
2021-04-06 Added TPS54331DR symbol
2021-04-06 Display test
2022-01-29 Migrate to Kicad 6
2022-01-29 Rename from stm32 to v2 custom pcb
2022-01-29 Add RP2040 lib
